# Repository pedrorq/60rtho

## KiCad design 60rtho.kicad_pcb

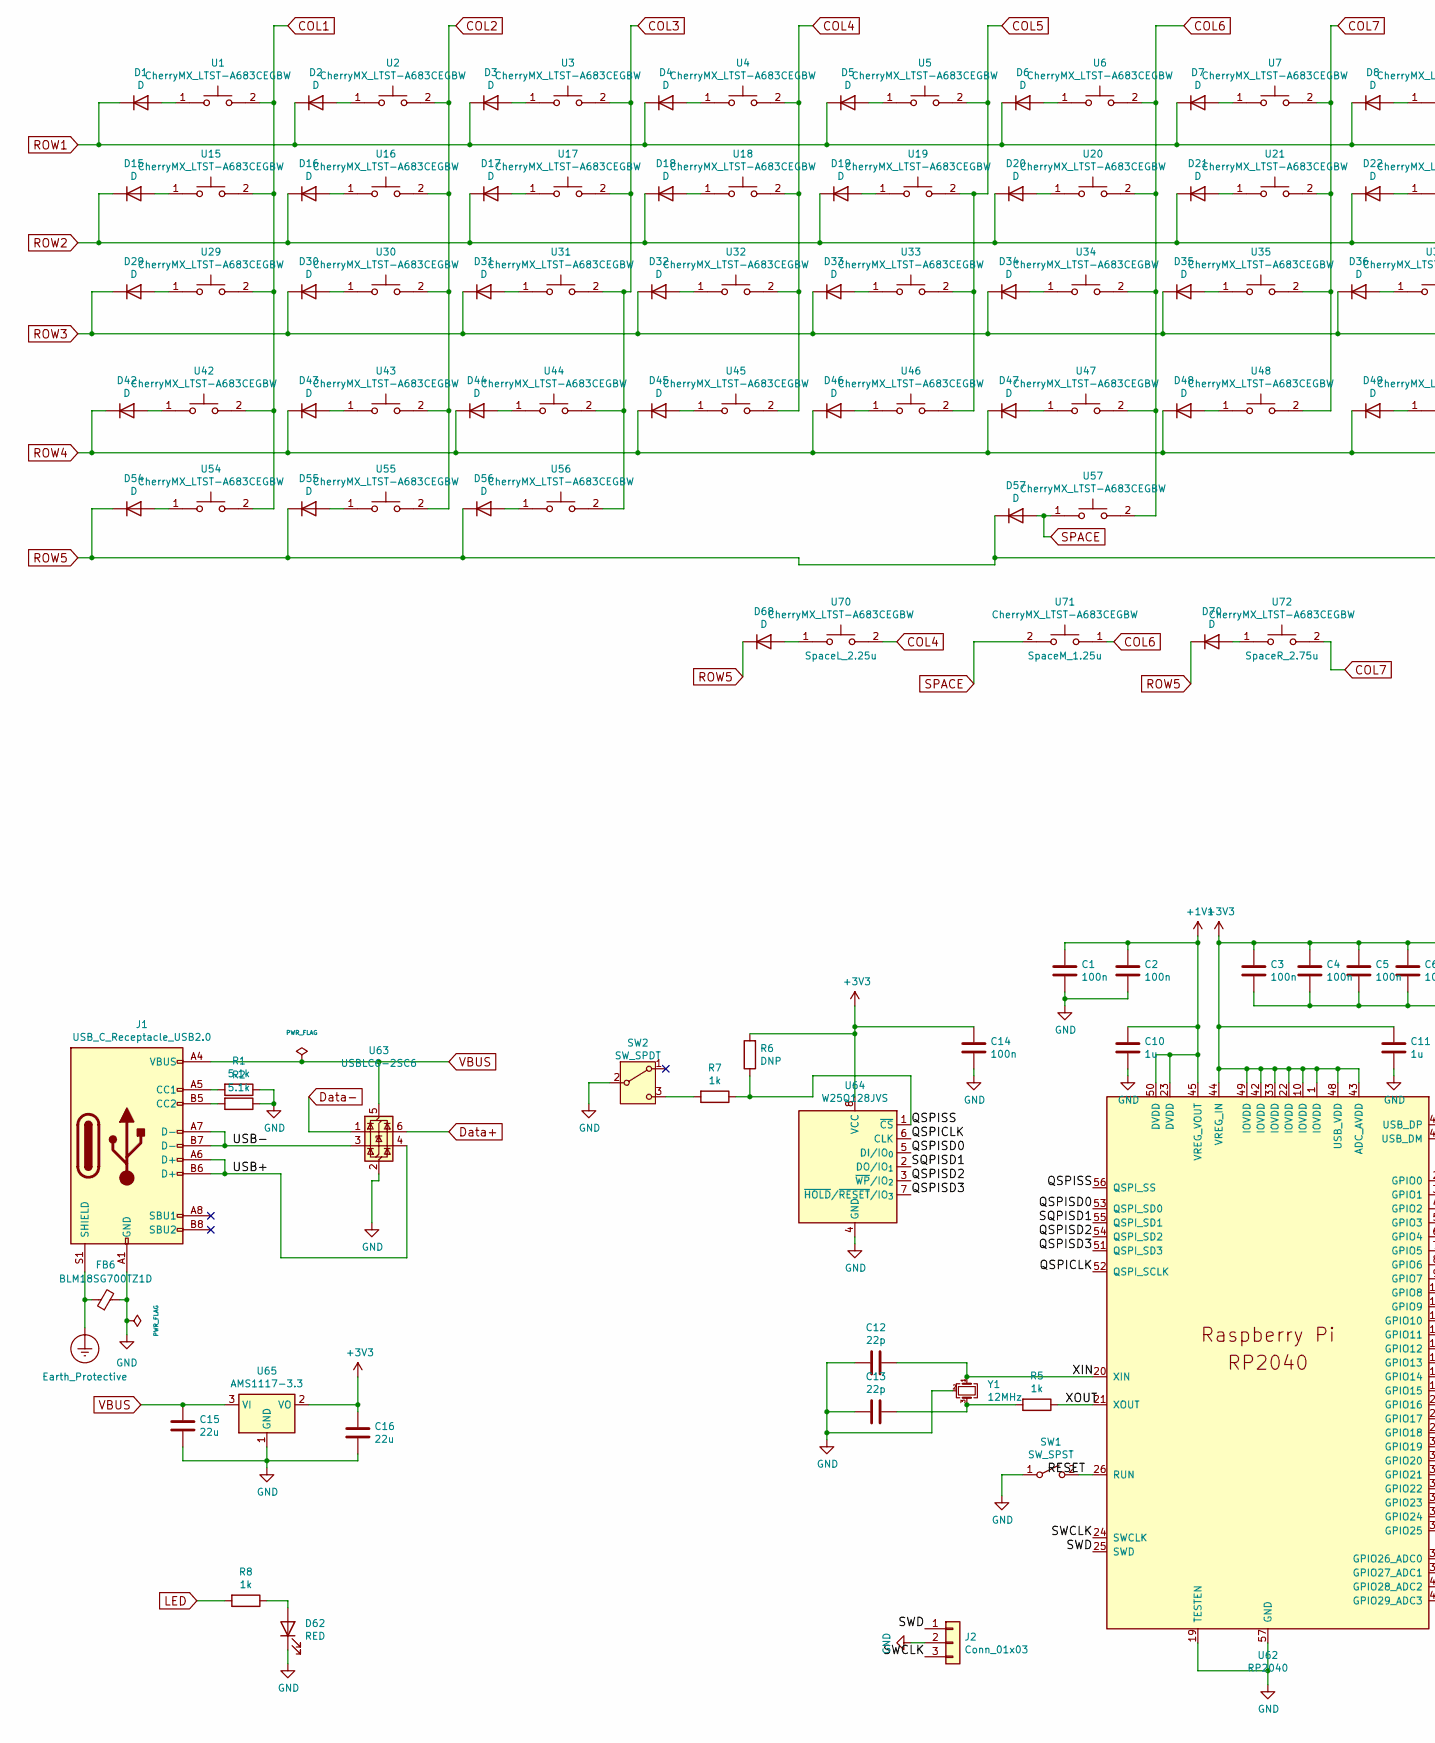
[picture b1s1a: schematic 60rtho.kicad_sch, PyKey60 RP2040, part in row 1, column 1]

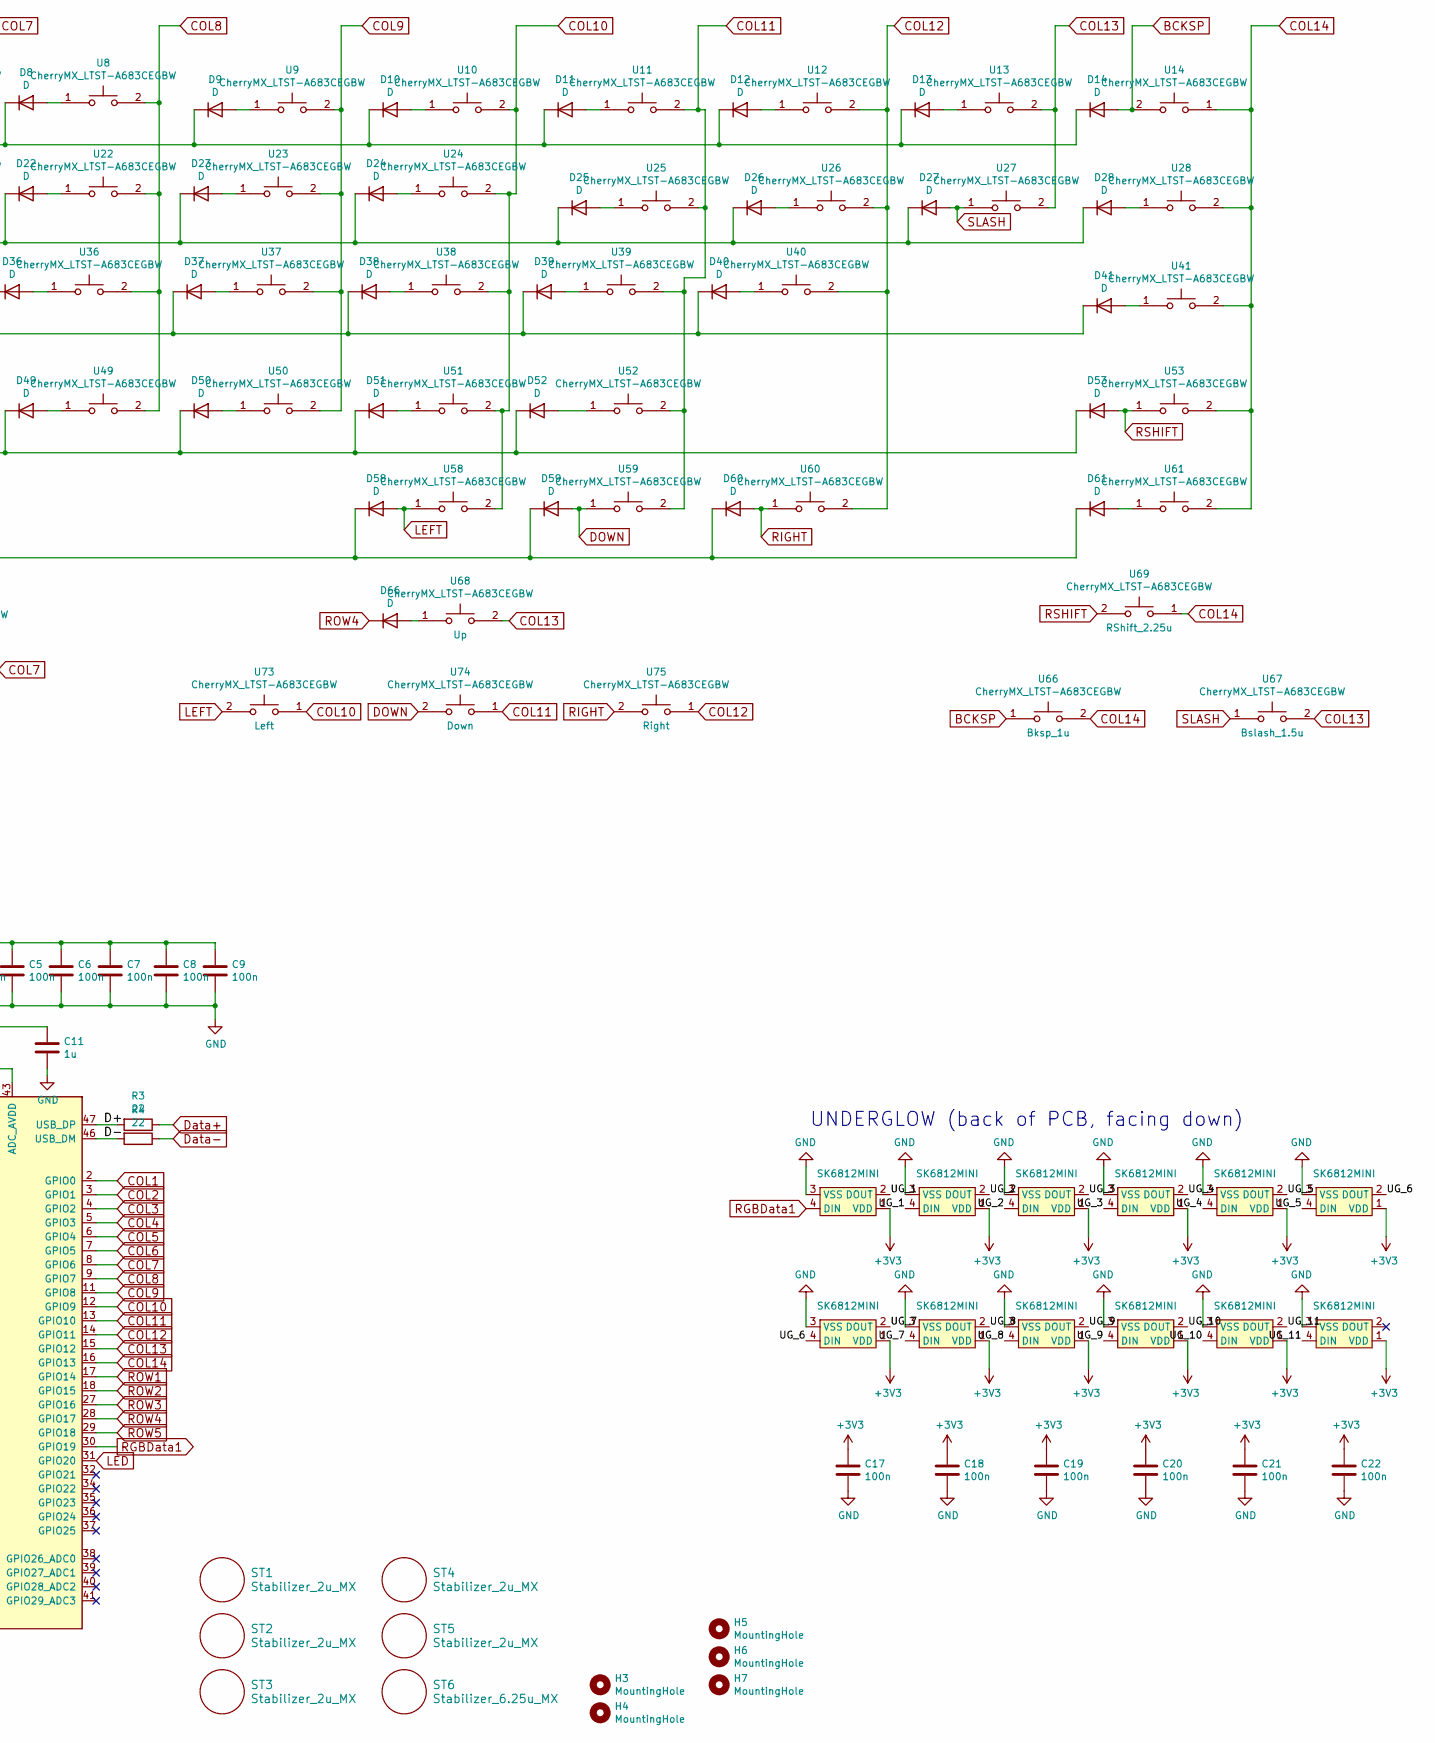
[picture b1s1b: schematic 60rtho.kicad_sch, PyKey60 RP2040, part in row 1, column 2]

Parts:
C1, C2, C3, C4, C5, C6, C7, C8, C9, C14, C17, C18, C19, C20, C21, C22: 100n; C_0603_1608Metric; LCSC C14663
C10, C11: 1u; C_0603_1608Metric; LCSC C15849
C12, C13: 22p; C_0603_1608Metric; LCSC C1653
C15, C16: 22u; C_0603_1608Metric; LCSC C59461
D1, D2, D3, D4, D5, D6, D7, D8, D9, D10, D11, D12, D13, D14, D15, D16, D17, D18, D19, D20, D21, D22, D23, D24, D25, D26, D27, D28, D29, D30, D31, D32, D33, D34, D35, D36, D37, D38, D39, D40, D41, D42, D43, D44, D45, D46, D47, D48, D49, D50, D51, D52, D53, D54, D55, D56, D57, D58, D59, D60, D61, D66, D68, D70: D; D_SOD-123
D62: RED; LED_0603_1608Metric; LCSC C2286
FB6: BLM18SG700TZ1D; C_0603_1608Metric_Pad1.08x0.95mm_HandSolder; LCSC C1002
H3, H5: MountingHole; PKRHSL
H4, H6: MountingHole; PKRH
H7: MountingHole; KB_BlueMicro
J1: USB_C_Receptacle_USB2.0; USB_C_Receptacle_HRO_TYPE-C-31-M-12
J2: Conn_01x03; PinHeader_1x03_P2.00mm_Vertical
LED1, LED2, LED3, LED4, LED5, LED6, LED7, LED8, LED9, LED10, LED11, LED12: SK6812MINI; LED_SK6812MINI_PLCC4_3.5x3.5mm_P1.75mm
R1, R2: 5.1k; R_0603_1608Metric; LCSC C23186
R3, R4: 22; R_0603_1608Metric; LCSC C23345
R5, R7, R8: 1k; R_0603_1608Metric; LCSC C21190
R6: DNP; R_0603_1608Metric
ST1, ST2, ST3, ST4, ST5: Stabilizer_2u_MX; Stabilizer_Cherry_MX_2.00u
ST6: Stabilizer_6.25u_MX; Stabilizer_Cherry_MX_6.25u
SW1: SW_SPST; SW_Push_SPST_NO_Alps_SKRK
SW2: SW_SPDT; SW_SPDT_PCM12
U1, U2, U3, U4, U5, U6, U7, U8, U9, U10, U11, U12, U13, U14, U15, U16, U17, U18, U19, U20, U21, U22, U23, U24, U25, U26, U27, U28, U29, U30, U31, U32, U33, U34, U35, U36, U37, U38, U39, U40, U41, U42, U43, U44, U45, U46, U47, U48, U49, U50, U51, U52, U53, U54, U55, U56, U57, U58, U59, U60, U61, U66, U67, U68, U69, U70, U71, U72, U73, U74, U75: CherryMX_LTST-A683CEGBW; SW_MX_HotSwap_reinforced
U62: RP2040; RP2040-QFN-56; LCSC C2040
U63: USBLC6-2SC6; SOT-23-6; LCSC C558442
U64: W25Q128JVS; SOIC-8_5.23x5.23mm_P1.27mm; LCSC C97521
U65: AMS1117-3.3; SOT-223-3_TabPin2; LCSC C6186
Y1: 12MHz; Crystal_SMD_3225-4Pin_3.2x2.5mm; LCSC C93114

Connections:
+1V1: C1.1, C2.1, C10.1, U62.23 (DVDD), U62.45 (VREG_VOUT), U62.50 (DVDD)
+3V3: C3.1, C4.1, C5.1, C6.1, C7.1, C8.1, C9.1, C11.1, C14.1, C16.1, C17.1, C18.1, C19.1, C20.1, C21.1, C22.1, LED1.1 (VDD), LED2.1 (VDD), LED3.1 (VDD), LED4.1 (VDD), LED5.1 (VDD), LED6.1 (VDD), LED7.1 (VDD), LED8.1 (VDD), LED9.1 (VDD), LED10.1 (VDD), LED11.1 (VDD), LED12.1 (VDD), R6.2, U62.1 (IOVDD), U62.10 (IOVDD), U62.22 (IOVDD), U62.33 (IOVDD), U62.42 (IOVDD), U62.43 (ADC_AVDD), U62.44 (VREG_IN), U62.48 (USB_VDD), U62.49 (IOVDD), U64.8 (VCC), U65.2 (VO)
/D+: R3.2, U62.47 (USB_DP)
/D-: R4.2, U62.46 (USB_DM)
/QSPICLK: U62.52 (QSPI_SCLK), U64.6 (CLK)
/QSPISD0: U62.53 (QSPI_SD0), U64.5 (DI/IO_{0})
/QSPISD2: U62.54 (QSPI_SD2), U64.3 (~WP/IO_{2})
/QSPISD3: U62.51 (QSPI_SD3), U64.7 (~HOLD/~RESET/IO_{3})
/QSPISS: R6.1, R7.1, U62.56 (QSPI_SS), U64.1 (~CS)
/RESET: SW1.2 (B), U62.26 (RUN)
/SQPISD1: U62.55 (QSPI_SD1), U64.2 (DO/IO_{1})
/SWCLK: J2.3, U62.24 (SWCLK)
/SWD: J2.1, U62.25 (SWD)
/UG_1: LED1.2 (DOUT), LED2.4 (DIN)
/UG_2: LED2.2 (DOUT), LED3.4 (DIN)
/UG_3: LED3.2 (DOUT), LED4.4 (DIN)
/UG_4: LED4.2 (DOUT), LED5.4 (DIN)
/UG_5: LED5.2 (DOUT), LED6.4 (DIN)
/UG_6: LED6.2 (DOUT), LED7.4 (DIN)
/UG_7: LED7.2 (DOUT), LED8.4 (DIN)
/UG_8: LED8.2 (DOUT), LED9.4 (DIN)
/UG_9: LED9.2 (DOUT), LED10.4 (DIN)
/UG_10: LED10.2 (DOUT), LED11.4 (DIN)
/UG_11: LED11.2 (DOUT), LED12.4 (DIN)
/USB+: J1.A6 (D+), J1.B6 (D+), U63.4 (I/O2)
/USB-: J1.A7 (D-), J1.B7 (D-), U63.3 (I/O2)
/XIN: C12.1, U62.20 (XIN), Y1.1
/XOUT: R5.1, U62.21 (XOUT)
BCKSP: D14.2 (A), U14.2, U66.1
COL1: U1.2, U15.2, U29.2, U42.2, U54.2, U62.2 (GPIO0)
COL2: U2.2, U16.2, U30.2, U43.2, U55.2, U62.3 (GPIO1)
COL3: U3.2, U17.2, U31.2, U44.2, U56.2, U62.4 (GPIO2)
COL4: U4.2, U18.2, U32.2, U45.2, U62.5 (GPIO3), U70.2
COL5: U5.2, U19.2, U33.2, U46.2, U62.6 (GPIO4)
COL6: U6.2, U20.2, U34.2, U47.2, U57.2, U62.7 (GPIO5), U71.1
COL7: U7.2, U21.2, U35.2, U48.2, U62.8 (GPIO6), U72.2
COL8: U8.2, U22.2, U36.2, U49.2, U62.9 (GPIO7)
COL9: U9.2, U23.2, U37.2, U50.2, U62.11 (GPIO8)
COL10: U10.2, U24.2, U38.2, U51.2, U58.2, U62.12 (GPIO9), U73.1
COL11: U11.2, U25.2, U39.2, U52.2, U59.2, U62.13 (GPIO10), U74.1
COL12: U12.2, U26.2, U40.2, U60.2, U62.14 (GPIO11), U75.1
COL13: U13.2, U27.2, U62.15 (GPIO12), U67.2, U68.2
COL14: U14.1, U28.2, U41.2, U53.2, U61.2, U62.16 (GPIO13), U66.2, U69.1
DOWN: D59.2 (A), U59.1, U74.2
Data+: R3.1, U63.6 (I/O1)
Data-: R4.1, U63.1 (I/O1)
Earth_Protective: FB6.1, J1.S1 (SHIELD)
GND: C1.2, C2.2, C3.2, C4.2, C5.2, C6.2, C7.2, C8.2, C9.2, C10.2, C11.2, C12.2, C13.2, C14.2, C15.2, C16.2, C17.2, C18.2, C19.2, C20.2, C21.2, C22.2, D62.1 (K), FB6.2, J1.A1 (GND), J1.A12 (GND), J1.B1 (GND), J1.B12 (GND), J2.2, LED1.3 (VSS), LED2.3 (VSS), LED3.3 (VSS), LED4.3 (VSS), LED5.3 (VSS), LED6.3 (VSS), LED7.3 (VSS), LED8.3 (VSS), LED9.3 (VSS), LED10.3 (VSS), LED11.3 (VSS), LED12.3 (VSS), R1.1, R2.1, SW1.1 (A), SW2.2 (B), U62.19 (TESTEN), U62.57 (GND), U63.2 (GND), U64.4 (GND), U65.1 (GND), Y1.2 (G), Y1.4 (G)
LED: R8.2, U62.31 (GPIO20)
LEFT: D58.2 (A), U58.1, U73.2
unnamed: C13.1, R5.2, Y1.3
unnamed: D1.2 (A), U1.1
unnamed: D2.2 (A), U2.1
unnamed: D3.2 (A), U3.1
unnamed: D4.2 (A), U4.1
unnamed: D5.2 (A), U5.1
unnamed: D6.2 (A), U6.1
unnamed: D7.2 (A), U7.1
unnamed: D8.2 (A), U8.1
unnamed: D9.2 (A), U9.1
unnamed: D10.2 (A), U10.1
unnamed: D11.2 (A), U11.1
unnamed: D12.2 (A), U12.1
unnamed: D13.2 (A), U13.1
unnamed: D15.2 (A), U15.1
unnamed: D16.2 (A), U16.1
unnamed: D17.2 (A), U17.1
unnamed: D18.2 (A), U18.1
unnamed: D19.2 (A), U19.1
unnamed: D20.2 (A), U20.1
unnamed: D21.2 (A), U21.1
unnamed: D22.2 (A), U22.1
unnamed: D23.2 (A), U23.1
unnamed: D24.2 (A), U24.1
unnamed: D25.2 (A), U25.1
unnamed: D26.2 (A), U26.1
unnamed: D28.2 (A), U28.1
unnamed: D29.2 (A), U29.1
unnamed: D30.2 (A), U30.1
unnamed: D31.2 (A), U31.1
unnamed: D32.2 (A), U32.1
unnamed: D33.2 (A), U33.1
unnamed: D34.2 (A), U34.1
unnamed: D35.2 (A), U35.1
unnamed: D36.2 (A), U36.1
unnamed: D37.2 (A), U37.1
unnamed: D38.2 (A), U38.1
unnamed: D39.2 (A), U39.1
unnamed: D40.2 (A), U40.1
unnamed: D41.2 (A), U41.1
unnamed: D42.2 (A), U42.1
unnamed: D43.2 (A), U43.1
unnamed: D44.2 (A), U44.1
unnamed: D45.2 (A), U45.1
unnamed: D46.2 (A), U46.1
unnamed: D47.2 (A), U47.1
unnamed: D48.2 (A), U48.1
unnamed: D49.2 (A), U49.1
unnamed: D50.2 (A), U50.1
unnamed: D51.2 (A), U51.1
unnamed: D52.2 (A), U52.1
unnamed: D54.2 (A), U54.1
unnamed: D55.2 (A), U55.1
unnamed: D56.2 (A), U56.1
unnamed: D61.2 (A), U61.1
unnamed: D62.2 (A), R8.1
unnamed: D66.2 (A), U68.1
unnamed: D68.2 (A), U70.1
unnamed: D70.2 (A), U72.1
unnamed: J1.A5 (CC1), R1.2
unnamed: J1.B5 (CC2), R2.2
unnamed: R7.2, SW2.3 (C)
RGBData1: LED1.4 (DIN), U62.30 (GPIO19)
RIGHT: D60.2 (A), U60.1, U75.2
ROW1: D1.1 (K), D2.1 (K), D3.1 (K), D4.1 (K), D5.1 (K), D6.1 (K), D7.1 (K), D8.1 (K), D9.1 (K), D10.1 (K), D11.1 (K), D12.1 (K), D13.1 (K), D14.1 (K), U62.17 (GPIO14)
ROW2: D15.1 (K), D16.1 (K), D17.1 (K), D18.1 (K), D19.1 (K), D20.1 (K), D21.1 (K), D22.1 (K), D23.1 (K), D24.1 (K), D25.1 (K), D26.1 (K), D27.1 (K), D28.1 (K), U62.18 (GPIO15)
ROW3: D29.1 (K), D30.1 (K), D31.1 (K), D32.1 (K), D33.1 (K), D34.1 (K), D35.1 (K), D36.1 (K), D37.1 (K), D38.1 (K), D39.1 (K), D40.1 (K), D41.1 (K), U62.27 (GPIO16)
ROW4: D42.1 (K), D43.1 (K), D44.1 (K), D45.1 (K), D46.1 (K), D47.1 (K), D48.1 (K), D49.1 (K), D50.1 (K), D51.1 (K), D52.1 (K), D53.1 (K), D66.1 (K), U62.28 (GPIO17)
ROW5: D54.1 (K), D55.1 (K), D56.1 (K), D57.1 (K), D58.1 (K), D59.1 (K), D60.1 (K), D61.1 (K), D68.1 (K), D70.1 (K), U62.29 (GPIO18)
RSHIFT: D53.2 (A), U53.1, U69.2
SLASH: D27.2 (A), U27.1, U67.1
SPACE: D57.2 (A), U57.1, U71.2
VBUS: C15.1, J1.A4 (VBUS), J1.A9 (VBUS), J1.B4 (VBUS), J1.B9 (VBUS), U63.5 (VBUS), U65.3 (VI)

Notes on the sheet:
UNDERGLOW (back of PCB, facing down)

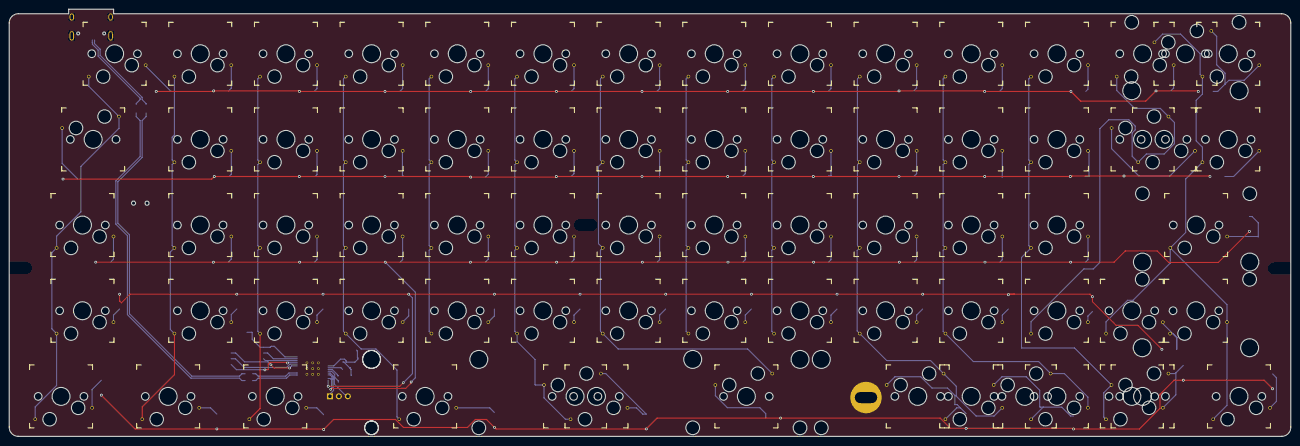
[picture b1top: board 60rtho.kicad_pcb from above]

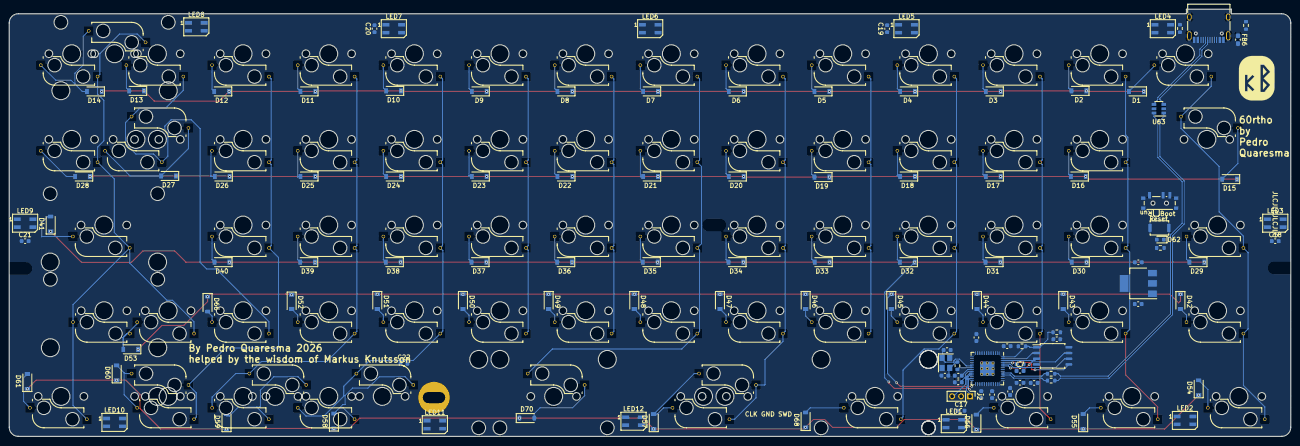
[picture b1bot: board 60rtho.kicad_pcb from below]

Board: 2 copper layers, 285.0 x 95.0 mm, 199 parts (118 on the bottom side), 123 nets.

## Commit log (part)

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2026-06-16 Fixed schematic

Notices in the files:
60rtho.kicad_pcb:
License: CERN-OHL-W (CERN OHL v2)
